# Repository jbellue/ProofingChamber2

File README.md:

# Proofing Chamber 2

A smart, temperature-controlled proofing chamber project.

## Repository Structure

- firmware/ — ESP32 firmware (PlatformIO)
- hardware/ — KiCad designs and vendor references
  - boards/ — device PCB projects
  - libraries/ — project symbols/footprints
  - docs/ — exports (PDFs, BOMs)
  - third_party/ — external references (git submodules)

## Quick Start

### Building the Firmware

There are several ways to build the firmware:

#### Option 1: Using the Build Script (Recommended for Automation)

```bash
./build.sh
```

This script will:
- Install PlatformIO if not already present
- Build the firmware automatically
- Provide clear error messages if something goes wrong

**For Restricted Environments (No Internet):**
```bash
./build.sh --check  # Syntax checking only
```

### Running Unit Tests

The firmware includes unit tests with mocked Arduino/ESP32 libraries:

```bash
./run-tests.sh
# or
make test
```

Tests run completely offline and don't require hardware or the ESP32 platform. See `firmware/test/README.md` for details.

This performs syntax checking without downloading ESP32 platform packages.

#### Option 2: Using Make

```bash
make all      # Install PlatformIO and build
make build    # Build only (assumes PlatformIO is installed)
make check    # Syntax check only (works offline)
make clean    # Clean build artifacts
```

Run `make help` for all available targets.

#### Option 3: Using PlatformIO Directly

```bash
cd firmware
pio run
```

**Prerequisites:**
- Python 3.6 or later
- pip (Python package installer)
- Internet connection (for first build to download platform packages and dependencies)

**Note:** The first build will take longer as PlatformIO downloads the ESP32 platform and required libraries.

### Workaround for Restricted Environments

If you're in an environment where internet access is restricted (e.g., some CI systems, air-gapped networks), you can use the **syntax checking** feature:

```bash
# Using build script
./build.sh --check

# Or using make
make check
```

This validates C++ syntax without requiring ESP32 platform downloads. While it can't produce a firmware binary, it verifies code structure and catches syntax errors.

### Hardware Vendor References

If the repository was cloned without submodules, fetch them:

```
git submodule update --init --recursive
```

## Detailed Docs

- See firmware details in firmware/README.md
- Hardware-specific docs live under hardware/ (or board project folders)

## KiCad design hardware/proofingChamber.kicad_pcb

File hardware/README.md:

OLED symbol and footprint: https://www.snapeda.com/parts/OLED%20128x64%201.3%22%20I2C/UNIVERSAL-SOLDER%20Electronics%20Ltd/view-part/
OLED 3d model: https://grabcad.com/library/1-3-oled-display-128x64-1

Encoder 3d model: https://www.snapeda.com/parts/PEC11R-4020F-S0024/Bourns/view-part/

ESP32-C3: https://www.snapeda.com/parts/ESP32-C3%20SuperMini_TH/Espressif%20Systems/view-part/

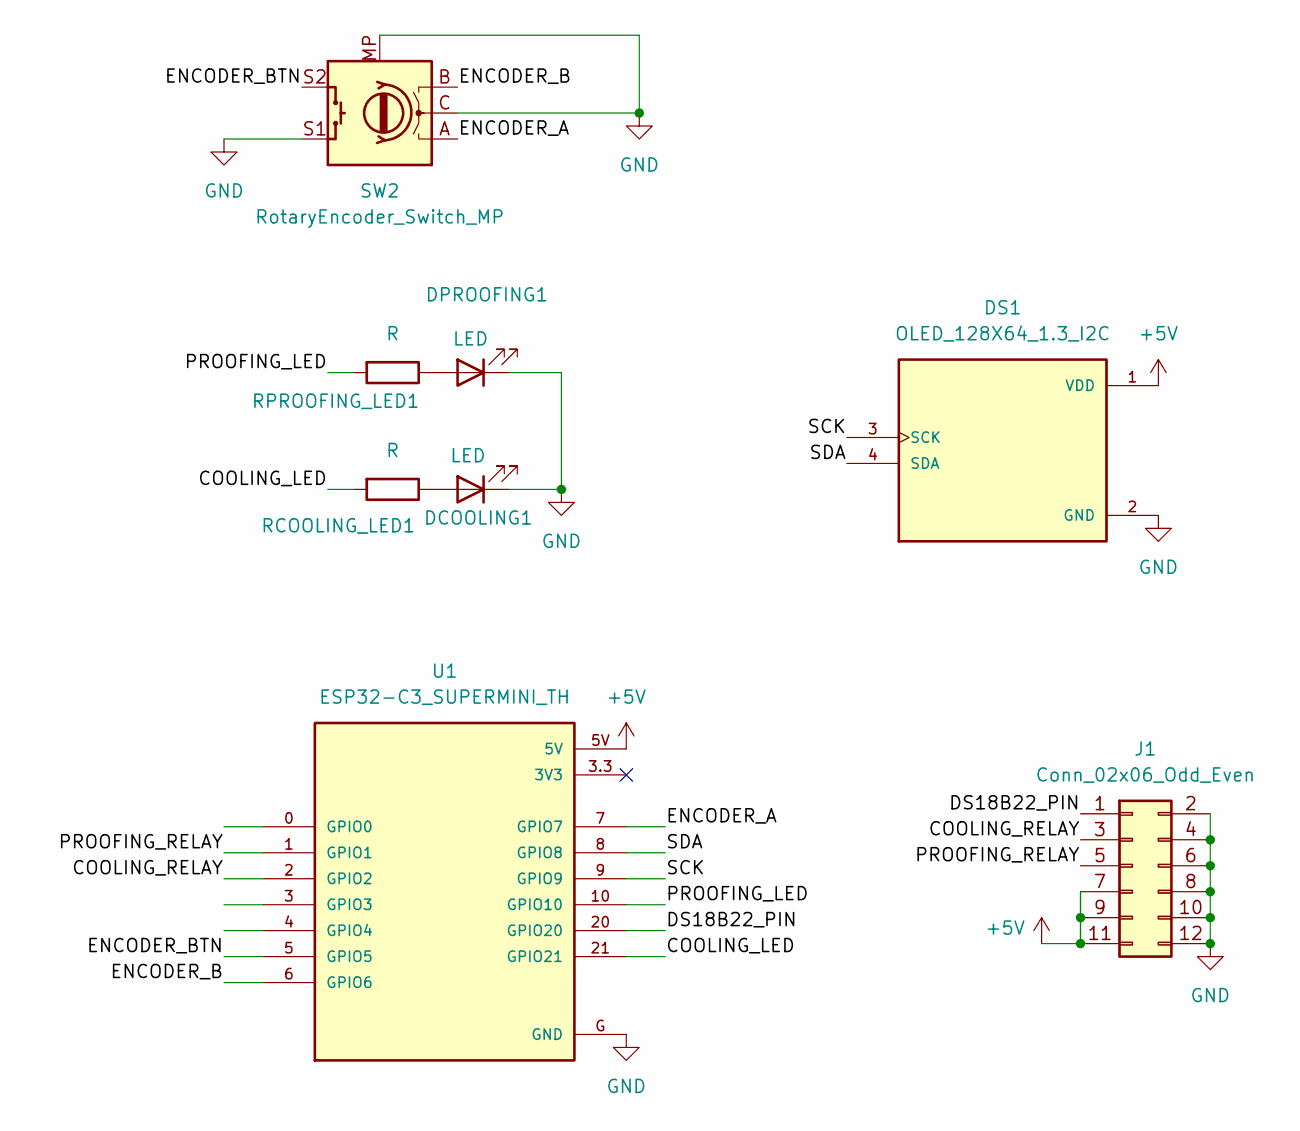
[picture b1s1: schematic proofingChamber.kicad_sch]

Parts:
DCOOLING1: LED; LED_D3.0mm
DPROOFING1: LED; LED_D3.0mm
DS1: OLED_128X64_1.3_I2C; LCD_OLED_128X64_1.3_I2C; PARTREV NA
J1: Conn_02x06_Odd_Even; PinSocket_2x06_P2.54mm_Horizontal
RCOOLING_LED1: R; R_Axial_DIN0207_L6.3mm_D2.5mm_P7.62mm_Horizontal
RPROOFING_LED1: R; R_Axial_DIN0207_L6.3mm_D2.5mm_P7.62mm_Horizontal
SW2: RotaryEncoder_Switch_MP; RotaryEncoder_Alps_EC11E-Switch_Vertical_H20mm
U1: ESP32-C3_SUPERMINI_TH; MODULE_ESP32-C3_SUPERMINI_TH

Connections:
+5V: DS1.1 (VDD), J1.7, J1.9, J1.11, U1.5V
/COOLING_LED: RCOOLING_LED1.2, U1.21 (GPIO21)
/COOLING_RELAY: J1.3, U1.2 (GPIO2)
/DS18B22_PIN: J1.1, U1.20 (GPIO20)
/ENCODER_A: SW2.A, U1.7 (GPIO7)
/ENCODER_B: SW2.B, U1.6 (GPIO6)
/ENCODER_BTN: SW2.S2, U1.5 (GPIO5)
/PROOFING_LED: RPROOFING_LED1.2, U1.10 (GPIO10)
/PROOFING_RELAY: J1.5, U1.1 (GPIO1)
/SCK: DS1.3 (SCK), U1.9 (GPIO9)
/SDA: DS1.4 (SDA), U1.8 (GPIO8)
GND: DCOOLING1.1 (K), DPROOFING1.1 (K), DS1.2 (GND), J1.2, J1.4, J1.6, J1.8, J1.10, J1.12, SW2.C, SW2.MP, SW2.S1, U1.G (GND)
unnamed: DCOOLING1.2 (A), RCOOLING_LED1.1
unnamed: DPROOFING1.2 (A), RPROOFING_LED1.1

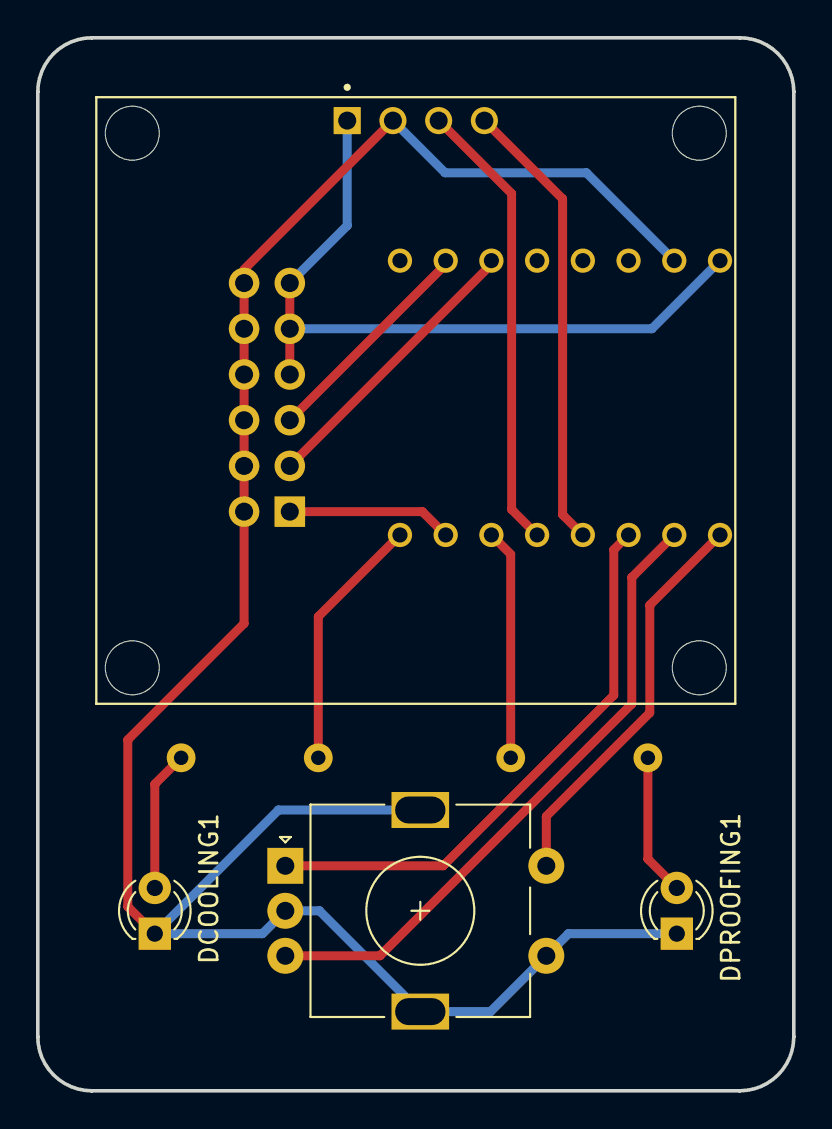
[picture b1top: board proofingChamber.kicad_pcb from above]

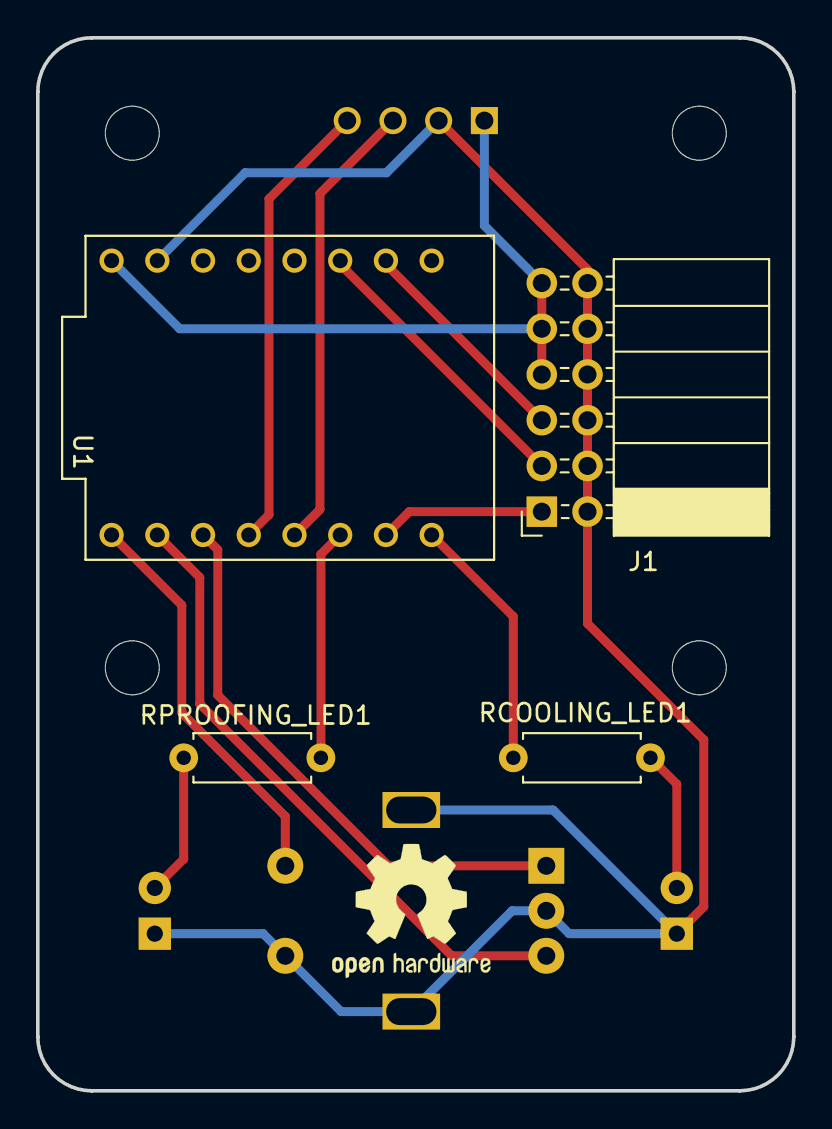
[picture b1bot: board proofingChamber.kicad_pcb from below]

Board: 2 copper layers, 42.0 x 58.5 mm, 8 parts (4 on the bottom side), 14 nets.

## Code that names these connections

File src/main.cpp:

#include <U8g2lib.h>
#include "DebugUtils.h"
#include "DisplayManager.h"
#include "InputManager.h"
#include "MenuActions.h"
#include "MenuItems.h"
#include "screens/Initialization.h"
#include "screens/Menu.h"
#include "services/RebootService.h"
#include "services/NetworkService.h"
#include "services/StorageAdapter.h"
#include "services/IStorage.h"
#include "screens/controllers/ProofingController.h"
#include "screens/controllers/AdjustTimeController.h"
#include "screens/controllers/AdjustValueController.h"
#include "screens/controllers/RebootController.h"
#include "screens/controllers/WiFiResetController.h"
#include "screens/controllers/CoolingController.h"
#include "screens/controllers/DataDisplayController.h"
#include "screens/controllers/ConfirmTimezoneController.h"
#include "screens/controllers/PowerOffController.h"
#include "screens/views/AdjustValueView.h"
#include "screens/views/AdjustTimeView.h"
#include "screens/views/CoolingView.h"
#include "screens/views/ProofingView.h"
#include "screens/views/RebootView.h"
#include "screens/views/WiFiResetView.h"
#include "screens/views/DataDisplayView.h"
#include "screens/views/ConfirmTimezoneView.h"
#include "screens/views/PowerOffView.h"
#include "ScreensManager.h"
#include "Storage.h"
#include "TemperatureController.h"
#include "AppContextDecl.h"

#define DS18B20_PIN       0
#define COOLING_RELAY_PIN 1
#define HEATING_RELAY_PIN 2
#define COOLING_LED_PIN   10
#define PROOFING_LED_PIN  6
#define ENCODER_CLK       3
#define ENCODER_DT        4
#define ENCODER_SW        5

// Global objects
DisplayManager displayManager(U8G2_R0);
// Storage adapter and temperature controller depend on storage
services::StorageAdapter storageAdapter;
TemperatureController temperatureController(HEATING_RELAY_PIN, COOLING_RELAY_PIN, PROOFING_LED_PIN, COOLING_LED_PIN);

ScreensManager screensManager;
InputManager inputManager(ENCODER_CLK, ENCODER_DT, ENCODER_SW, DS18B20_PIN);
// Global AppContext instance (defined early so globals can receive its pointer)
AppContext appContext;

// Static controller instances (stack allocated)
static AdjustValueController adjustValueControllerInstance(&appContext);
static AdjustTimeController adjustTimeControllerInstance(&appContext);
static ProofingController proofingControllerInstance(&appContext);
static RebootController rebootInstance(&appContext);
static CoolingController coolingControllerInstance(&appContext);
static WiFiResetController wifiResetControllerInstance(&appContext);
static DataDisplayController dataDisplayControllerInstance(&appContext);
static ConfirmTimezoneController confirmTimezoneControllerInstance(&appContext);
static PowerOffController powerOffControllerInstance(&appContext);

AdjustValueController* adjustValueController = &adjustValueControllerInstance;
AdjustTimeController* adjustTimeController = &adjustTimeControllerInstance;
ProofingController* proofingController = &proofingControllerInstance;
RebootController* reboot = &rebootInstance;
CoolingController* coolingController = &coolingControllerInstance;
WiFiResetController* wifiResetController = &wifiResetControllerInstance;
DataDisplayController* dataDisplayController = &dataDisplayControllerInstance;
ConfirmTimezoneController* confirmTimezoneController = &confirmTimezoneControllerInstance;
PowerOffController* powerOffController = &powerOffControllerInstance;
Initialization* initialization = nullptr; // Created in setup after network service

MenuActions* menuActions = nullptr; // Created in setup
Menu* menu = nullptr; // Created in setup

// Network and reboot services
services::NetworkService networkService;
services::RebootService rebootService;

// Static view instances (allocated on stack)
static AdjustValueView adjustValueView(&displayManager);
static AdjustTimeView adjustTimeView(&displayManager);
static CoolingView coolingView(&displayManager);
static ProofingView proofingView(&displayManager);
static RebootView rebootView(&displayManager);
static WiFiResetView wifiResetView(&displayManager);
static DataDisplayView dataDisplayView(&displayManager);
static ConfirmTimezoneView confirmTimezoneView(&displayManager);
static PowerOffView powerOffView(&displayManager);

void setup() {
#if DEBUG
    // Initialize serial communication
    Serial.begin(115200);
#endif
    if (!storageAdapter.begin()) {
        DEBUG_PRINTLN("Storage initialization failed - using safe defaults");
        // Set safe default temperatures (moderate room temperature range)
        temperatureController.setDefaultLimits(23, 27);
    }
    displayManager.begin();
    inputManager.begin();
    temperatureController.begin();

    // Initialize LED pins as outputs
    pinMode(COOLING_LED_PIN, OUTPUT);
    pinMode(PROOFING_LED_PIN, OUTPUT);

    // Populate global AppContext so components can access shared services
    appContext.display = &displayManager;
    appContext.input = &inputManager;
    appContext.screens = &screensManager;
    appContext.tempController = &temperatureController;
    appContext.rebootService = &rebootService;
    appContext.networkService = &networkService;
    appContext.storage = &storageAdapter;
    appContext.encoderButtonPin = ENCODER_SW;
    
    // Add view pointers to AppContext
    appContext.adjustValueView = &adjustValueView;
    appContext.adjustTimeView = &adjustTimeView;
    appContext.coolingView = &coolingView;
    appContext.proofingView = &proofingView;
    appContext.rebootView = &rebootView;
    appContext.wifiResetView = &wifiResetView;
    appContext.dataDisplayView = &dataDisplayView;
    appContext.confirmTimezoneView = &confirmTimezoneView;
    appContext.powerOffView = &powerOffView;

    // Provide storage to TemperatureController now that AppContext.storage is set
    temperatureController.setStorage(appContext.storage);

    // Create remaining objects that depend on appContext being fully initialized
    static Initialization initializationInstance(&appContext);
    initialization = &initializationInstance;
    
    static MenuActions menuActionsInstance(&appContext, adjustValueController, adjustTimeController, proofingController, coolingController, wifiResetController, reboot, dataDisplayController, confirmTimezoneController, powerOffController);
    menuActions = &menuActionsInstance;
    
    static Menu menuInstance(&appContext, menuActions);
    menu = &menuInstance;
    
    // Initialize dynamic timezone menus
    initializeAllMenus(&appContext);
    
    // Set the menu instance in MenuActions for context-aware actions
    menuActions->setMenu(&menuInstance);

    initialization->setNextScreen(menu);
    screensManager.setActiveScreen(initialization);
}

void loop() {
    inputManager.update();
    screensManager.update();
}

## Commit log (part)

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2025-03-15 Refactor Menu::adjustValue for improved encoder handling and add updateAdjustValueDisplay for better display logic
2025-03-15 Initialize _oldPosition in adjustValue and setTime for accurate menu navigation
2025-03-16 Refactor display update functions to eliminate parameters and streamline menu navigation
2025-03-17 Update initialization messages for Wi-Fi and NTP connection in setup
2025-03-18 Add InputManager class for encoder handling and refactor Menu to utilize InputManager
2025-03-18 Only partially redraw the adjust screens
2025-03-23 Add getDisplayHeight method and modify drawTitle to accept initial Y position
2025-03-23 Add Initialization screen and refactor setup process for improved screen handling
2025-03-24 Refactor ProofingScreen to use struct tm for time handling and improve time display logic
2025-03-25 Refactor AdjustTime and AdjustValue classes to rename private member variables for display and input managers
2025-03-25 Refactor MenuActions to calculate end time dynamically using user input from AdjustTime
2025-03-25 Refactor CoolingScreen to improve button layout and display remaining time in a more user-friendly format
2025-03-28 Update encoder switch pin definition for consistency
2025-03-30 Update commitAverage method to accept a default value for averaging
2025-03-30 Initialize previous temperature to a high value for proper first update rendering
2025-03-31 Enhance InputManager to handle button press state and improve debounce logic
2025-03-31 Refactor AdjustTime to improve time display logic and add highlight functionality
2025-03-31 Refactor AdjustTime to allow cancelling
2025-04-01 Enhance DS18B20Manager error handling with retry logic and state management
2025-04-01 Refactor SimpleTime comparison logic and update AdjustTime validation to use operator overloads
2025-04-04 WIP - Add TemperatureController class for managing heating and cooling logic
2025-04-04 Add initialization check in InputManager to prevent re-initialization
2025-04-04 Add reboot functionality to MenuActions and implement Reboot screen
2025-04-07 Remove DS18B20Manager initialization from setup function
2025-04-07 Refactor DisplayManager to use u8g2_cb_t for display initialization and update method calls
2025-11-22 Refactor MenuActions and MenuItems to improve null checks and use lambda functions for action binding
2025-11-23 Refactor MenuActions to use AdjustTimeController and AdjustTimeView; remove AdjustTime implementation for improved structure and separation of concerns
2025-11-25 Refactor ProofingController and ProofingView for improved clarity and structure; streamline drawing methods and adjust icon positioning
2025-11-25 Refactor controllers to streamline drawing logic; move display logic to views and remove redundant methods
2025-11-27 Refactor TemperatureController to include proofing and cooling LED pins; update constructor and initialization logic for LED control
2025-11-28 Refactor CoolingController and CoolingView to improve temperature handling and display logic; remove unused variables and enhance drawing efficiency
2025-11-29 Refactor icon handling and view updates across controllers and views; streamline temperature and time drawing logic, and improve redraw efficiency.
2025-11-30 Refactor button handling in DisplayManager and controllers to support dynamic button arrays; streamline button drawing logic across views.
2025-11-30 Refactor CoolingView: update drawTitle method to accept time_t parameter and format title string; modify beginImpl in CoolingController to use new drawTitle implementation.
2025-11-30 Implement start method in ProofingView for streamlined initialization; update beginImpl in ProofingController to utilize new method for improved clarity and efficiency.
2025-11-30 Refactor RebootController and RebootView: streamline beginImpl to call view's start method; enhance RebootView to include drawButtons method for improved button rendering.
2025-12-01 Refactor: Introduce interfaces for Display, Input, and Temperature management
    - Created IDisplayManager, IInputManager, and ITemperatureController interfaces to define contracts for their respective implementations.
    - Updated DisplayManager, InputManager, and TemperatureController classes to implement their corresponding interfaces.
    - Replaced direct usage of concrete classes in AppContext with interface pointers for better abstraction and flexibility.
    - Introduced Null implementations (NullDisplayManager, NullInputManager, NullTemperatureController) to safely handle null cases using the Null Object Pattern.
    - Updated all relevant controllers and views to use the new interfaces and null impl
2025-12-01 Refactor: Replace global storage pointer with instance variable and add method for setting default temperature limits
2025-12-01 Refactor: Replace Screen class with BaseController in various controllers and related files for improved screen management and input handling
2025-12-06 Add drawTriangle method and update navigation hints for improved arrow rendering
2025-12-07 Add README.md with project overview, hardware details, features, and usage instructions
2025-12-07 Refactor: Use SafePtr to resolve display context in Menu initialization
2025-12-18 Add setCurrentMenu method to Menu for programmatic menu navigation
2026-01-01 Initial plan
2026-01-01 Fix comment clarity and remove redundant menu initialization
2026-01-01 Implement timezone selection icon updates and add refresh function
2026-01-01 Add safety bounds check for scrollbar height calculation
2026-01-02 Add vertical line drawing functionality to DisplayManager and NullDisplayManager
2026-01-02 Add note about I2C pins for OLED display
2026-01-02 Remove custom Arduino mocks in favor of ArduinoFake from lib_deps
2026-01-16 Refactor InputManager to enhance encoder handling and add ISR support for button and encoder events
2026-01-18 Add documentation and validation test for timezone generation
2026-01-18 Simplify to single flat timezone array with helper functions
    - Replace multiple continent arrays with one flat TIMEZONES[] array
    - Each timezone has continent embedded: {continent, name, posixString}
    - Add inline helper functions for continent queries:
    - getContinentCount(), getContinentName()
    - getTimezoneCount(), getTimezone()
    - findTimezoneIndex()
2026-01-18 Separate timezone helpers into TimezoneHelpers.h
    - Create new TimezoneHelpers.h with helper functions
    - Update generate_timezones.py to only output static data in Timezones.h
    - Move inline helper functions (getContinentCount, getContinentName, etc.) to TimezoneHelpers.h
    - Update MenuItems.cpp and MenuActions.cpp to include TimezoneHelpers.h
    - Update test_timezones.cpp to include TimezoneHelpers.h
    - Update README.md to document the new file structure
2026-01-20 Implement smooth menu scrolling with smart positioning
2026-01-20 Add algorithm header for min/max functions
2026-01-20 Improve clamping logic for uint8_t conversion safety
2026-01-21 Fix selection animation - separate scroll and selection movement
2026-01-21 Fix circular scrolling - support negative scroll offsets
2026-01-21 Fix small menu animation - remove special case for menus ≤4 items
2026-01-24 Fix menu item alignment with centered selection box
2026-01-24 Fix text vertical centering - adjust baseline for visual center
2026-01-24 Fine-tune text centering - adjust MENU_ITEM_Y_OFFSET to 4
2026-01-24 Fix text centering logic - calculate from fixed selected item position
2026-01-24 Implement integer-only positioning from screen center
2026-01-24 Calculate text offset from font metrics instead of hardcoding
2026-01-24 Fix position stability - use truncation instead of rounding for scrollPixelOffset
2026-01-24 Remove debug output - smooth scrolling complete
2026-01-24 Drain all pending encoder steps in single update cycle
2026-01-24 Address code review: Add algorithm header and debug logging
2026-01-24 Add clarifying comments for embedded code readability
2026-01-24 Add clarifying comment for hardcoded GPIO pin in power-off
2026-01-24 Add error handling for GPIO wakeup and fix comment
2026-01-24 Replace LittleFS with Preferences for ESP32 storage
2026-01-24 Fix: Correct dotIndex check and readStringFromFile return logic
2026-01-25 Refactor PowerOffController: remove redundant comments and fix include order
2026-01-25 Refactor temperature settings loading: streamline retrieval of lower and upper limits from storage
2026-01-26 Add comprehensive Arduino to ESP-IDF migration documentation
2026-01-26 Optimize graphics: reduce menu redraws, cache font metrics, document unused code
2026-01-26 Optimize view rendering: cache font metrics and string widths to reduce redundant calls
2026-01-28 Add ESP32-C3_SUPERMINI_TH footprint and import guide
    - Created a new KiCad footprint for the ESP32-C3_SUPERMINI_TH module, defining pads and graphical elements for fabrication and silkscreen layers.
    - Added an HTML file for redirecting users to the SnapEDA import guide for the new module.
2026-01-29 Refactor LED and relay control: replace digitalWrite with gpio_set_level for improved GPIO handling
2026-01-29 Refactor input manager handling: remove SafePtr usage for direct context access; delete unused Null* classes for cleaner codebase.
2026-01-30 Refactor code structure for improved readability and maintainability
2026-02-03 slight tweak to the schematics
2026-02-03 Remove documentation files - code optimizations only
2026-02-03 Add temperature validation and improve web UI documentation
2026-02-03 Add IP display, timing info on web, and controller state tracking
2026-02-03 Fix compilation error by adding controller includes
2026-02-03 Update documentation for menu actions integration
2026-02-03 Update web UI to use virtual controls and display current screen
2026-02-03 Add visual guide showing web interface layout and usage
2026-02-03 Add executive summary for WiFi persistence fix
2026-02-03 Add comprehensive documentation for port conflict fix
2026-02-03 Add comprehensive documentation for captive portal fix
2026-02-03 Add final comprehensive summary of all WiFi fixes
2026-02-03 Add comprehensive documentation for WiFi state fix
2026-02-03 Fix captive portal timeout - remove timeout so it stays open until configured
2026-02-03 Add comprehensive documentation for WiFiManager library version fix
2026-02-03 Fix WiFi credentials being erased - remove WiFi.disconnect to preserve saved credentials
2026-02-03 Add comprehensive documentation for exact version pinning fix
2026-02-03 Add final comprehensive summary of all 12 WiFi fixes
2026-02-03 Fix build by using tzapu/WiFiManager 2.0.17 instead of deprecated khoih-prog library
2026-02-03 Add aggressive AP initialization delays for ESP32-C3 captive portal visibility
2026-02-03 Fix captive portal not starting: force resetSettings before autoConnect and add 3min timeout
2026-02-04 Show full menu list and add support for all screen types on web interface
2026-02-04 Add direct API methods to controllers, remove brittle navigation simulation
2026-02-04 Fix type conversion error: include Menu.h to enable BaseController conversion
2026-02-05 Add WebSocket server for real-time display mirroring from Views to browser
2026-02-05 Remove status polling and display mirroring, prepare for data-driven approach
2026-02-05 Fix compilation errors in WebServerService
2026-02-05 Remove unused canvas and fix display refresh after web actions
2026-02-05 Fix incomplete type error: include IWebServerService.h in controllers
2026-02-05 Fix web/display sync: add periodic web updates and display refresh delays
2026-02-05 Fix broken screen when cancelling proofing from device
2026-02-05 Fix cooling cancellation, auto-start proofing on timer expiry, reduce redundant WebSocket updates
2026-02-05 Refactor WebSocket error handling and remove unused display command logic
2026-02-05 Implement client-initiated state request pattern
2026-02-05 Store timezone index to fix duplicate POSIX string issue
2026-02-06 Remove backward compatibility logic from timezone storage
2026-02-06 Remove startConfigPortal method from INetworkService and NetworkService implementations
2026-02-06 Remove virtual input injection methods from IInputManager and InputManager
